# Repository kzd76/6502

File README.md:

# 6502
Yet another Ben Eater sbc clone

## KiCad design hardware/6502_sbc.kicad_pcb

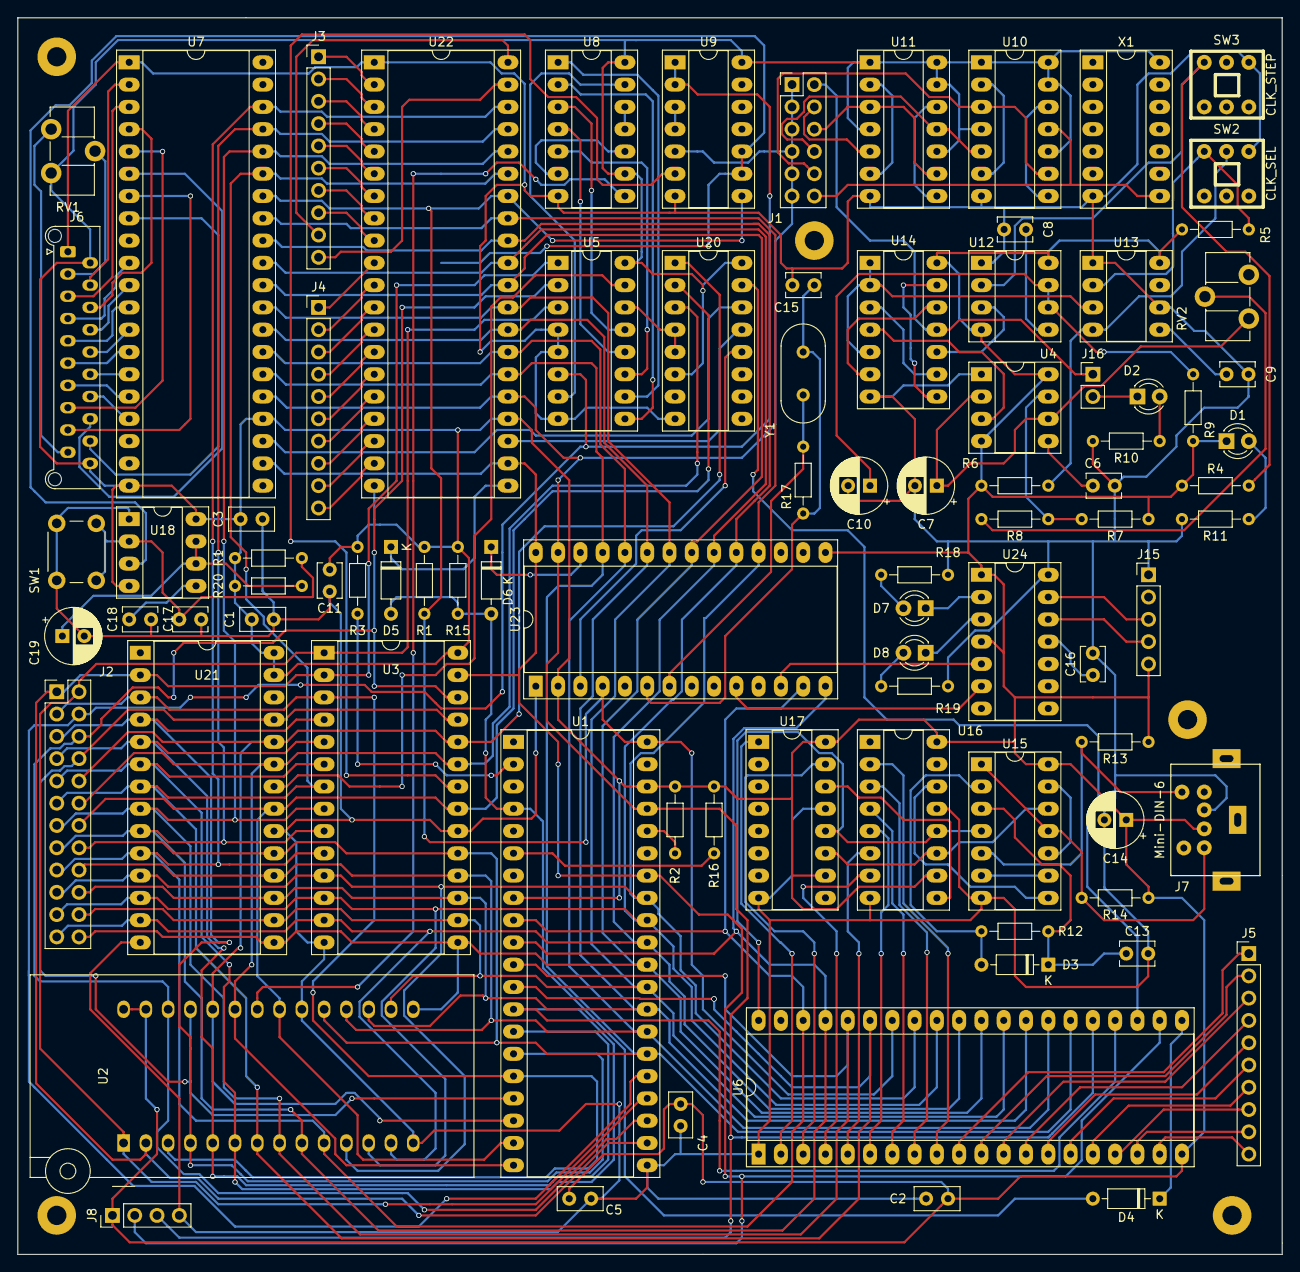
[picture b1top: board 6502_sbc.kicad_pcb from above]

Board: 2 copper layers, 144.1 x 141.0 mm, 92 parts (0 on the bottom side), 162 nets.

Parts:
C1, C2, C3, C4, C5: 100nF; C_Disc_D5.0mm_W2.5mm_P2.50mm
C6, C8, C9, C11, C13, C18: 0.01uF; C_Disc_D3.8mm_W2.6mm_P2.50mm
C7, C10: 1uF; CP_Radial_D6.3mm_P2.50mm
C14, C19: 10uF; CP_Radial_D6.3mm_P2.50mm
C15: 20pF; C_Disc_D3.8mm_W2.6mm_P2.50mm
C16: 470nF; C_Disc_D3.8mm_W2.6mm_P2.50mm
C17: 0.1uF; C_Disc_D3.8mm_W2.6mm_P2.50mm
D1, D2: LED; LED_D3.0mm
D3: 1N4148; D_DO-35_SOD27_P7.62mm_Horizontal
D4, D5, D6: SB140; D_DO-35_SOD27_P7.62mm_Horizontal
D7: LED_Rx; LED_D3.0mm
D8: LED_Tx; LED_D3.0mm
H1, H2, H3, H4, H5: MountingHole; MountingHole_2.2mm_M2_Pad
J1: CLK select; PinHeader_2x06_P2.54mm_Vertical
J2: Debug; PinHeader_2x12_P2.54mm_Vertical
J3: V3PA; PinHeader_1x10_P2.54mm_Vertical
J4: V3PB; PinHeader_1x10_P2.54mm_Vertical
J5: PORTA; PinHeader_1x10_P2.54mm_Vertical
J6: LCD; Molex_Picoflex_90325-0020_2x10_P1.27mm_Vertical
J7: Mini-DIN-6; Mini_din6
J8: SUP; PinHeader_1x04_P2.54mm_Vertical
J15: USB; PinHeader_1x05_P2.54mm_Vertical
J16: LED_EN; PinHeader_1x02_P2.54mm_Vertical
R1, R9, R17: 1M; R_Axial_DIN0204_L3.6mm_D1.6mm_P7.62mm_Horizontal
R1#2, R2, R3, R15, R16: 3.3k; R_Axial_DIN0204_L3.6mm_D1.6mm_P7.62mm_Horizontal
R4, R5, R6, R7, R8: 1k; R_Axial_DIN0204_L3.6mm_D1.6mm_P7.62mm_Horizontal
R10, R11, R18, R19: 220; R_Axial_DIN0204_L3.6mm_D1.6mm_P7.62mm_Horizontal
R12: 33k; R_Axial_DIN0204_L3.6mm_D1.6mm_P7.62mm_Horizontal
R13, R14: 5.6k; R_Axial_DIN0204_L3.6mm_D1.6mm_P7.62mm_Horizontal
R20: 47k; R_Axial_DIN0204_L3.6mm_D1.6mm_P7.62mm_Horizontal
RV1: R_POT; Potentiometer_ACP_CA9-H5_Horizontal
RV2: 1M; Potentiometer_ACP_CA9-H5_Horizontal
SW1: RESET; SW_PUSH_6mm_H5mm
SW2: CLK_SEL; BOTAO4
SW3: CLK_STEP; BOTAO4
U1: W65C02SxP; DIP-40_W15.24mm_Socket_LongPads
U2: 28C256; DIP_Socket-28_W11.9_W12.7_W15.24_W17.78_W18.5_3M_228-1277-0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
U3: HM62256BLP-7; DIP-28_W15.24mm_Socket_LongPads
U4, U12, U13, U18: NE555; DIP-8_W7.62mm_Socket_LongPads
U5, U20: 74LS138; DIP-16_W7.62mm_Socket_LongPads
U6, U7: W65C22SxP; DIP-40_W15.24mm_Socket_LongPads
U8: 74LS11; DIP-14_W7.62mm_Socket_LongPads
U9, U14: 74LS00; DIP-14_W7.62mm_Socket_LongPads
U10, U11: 74HC74; DIP-14_W7.62mm_Socket_LongPads
U15: 74HC14; DIP-14_W7.62mm_Socket_LongPads
U16, U17: 74HC595; DIP-16_W7.62mm_Socket_LongPads
U21: 28C64; DIP-28_W15.24mm_Socket_LongPads
U22: W65C22SxP-65xx; DIP-40_W15.24mm_Socket_LongPads
U23: W65C51-65xx; DIP-28_W15.24mm_Socket_LongPads
U24: MCP2221; DIP-14_W7.62mm_Socket_LongPads
X1: CXO_DIP14; DIP-14_W7.62mm_Socket_LongPads
Y1: 1,8432MHz; Crystal_HC18-U_Vertical

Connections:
+5V: C1.1, C2.1, C3.1, C4.1, C5.1, C11.2, C14.1, D1.1, J6.2, J6.20, J7.4, J8.1, J15.5, R1.1, R1#2.1, R2.1, R3.2, R4.1, R5.1, R6.1, R7.1, R9.1, R13.1, R14.1, R15.2, R16.2, R20.1, RV1.3, U1.8, U1.38, U2.27, U2.28, U3.28, U4.4, U4.8, U5.16, U6.20, U7.20, U7.24, U8.9, U8.14, U9.14, U10.1, U10.4, U10.10, U10.13, U10.14, U11.1, U11.4, U11.10, U11.13, U11.14, U12.4, U12.8, U13.8, U14.14, U15.14, U16.10, U16.16, U17.10, U17.16, U18.4, U18.8, U20.6, U20.16, U21.27, U21.28, U22.20, U22.24, U23.2, U23.15, U24.1, U24.4, X1.14
/0x9000: U5.14, U20.4, U20.5
/0x9000_LCD_VIA: U7.23, U20.14
/0x9200_KBD_VIA: U6.23, U20.15
/0x9400_3rd_VIA: U20.13, U22.23
/0x9600_ACIA: U20.12, U23.3
/0xA000: U5.13, U8.3
/0xB000: U5.12, U8.4
/0xC000: U5.11, U8.5
/0xD000: U5.10, U8.1
/0xE000: U5.9, U8.2
/0xF000: U5.7, U8.13
/A0: J2.17, U1.9, U2.10, U3.10, U6.38, U7.38, U21.10, U22.38, U23.13
/A1: J2.15, U1.10, U2.9, U3.9, U6.37, U7.37, U21.9, U22.37, U23.14
/A2: J2.13, U1.11, U2.8, U3.8, U6.36, U7.36, U21.8, U22.36
/A3: J2.11, U1.12, U2.7, U3.7, U6.35, U7.35, U21.7, U22.35
/A4: J2.9, U1.13, U2.6, U3.6, U6.24, U21.6
/A5: J2.7, U1.14, U2.5, U3.5, U21.5
/A6: J2.5, U1.15, U2.4, U3.4, U21.4
/A7: J2.3, U1.16, U2.3, U3.3, U21.3
/A8: J2.8, U1.17, U2.25, U3.25, U21.25
/A9: J2.10, U1.18, U2.24, U3.24, U20.1, U21.24
/A10: J2.14, U1.19, U2.21, U3.21, U20.2, U21.21
/A11: J2.12, U1.20, U2.23, U3.23, U20.3, U21.23
/A12: J2.1, U1.22, U2.2, U3.2, U5.1, U21.2
/A13: J2.6, U1.23, U2.26, U3.26, U5.2
/A14: J2.2, U1.24, U2.1, U3.1, U5.3
/A15: J2.4, U1.25, U5.6, U9.1, U9.2
/CLK: J1.1, J1.3, J1.5, J1.7, J1.9, J1.11, J8.3, U1.37, U6.25, U7.25, U9.5, U22.25, U23.27
/CLKSEL_1: R5.2, SW2.1, U13.2
/CLKSEL_2: R6.2, SW2.2, U13.4
/CLK_P1: C7.1, RV2.1, U4.2, U4.6
/CLK_P2: R8.2, RV2.2
/D0: J2.19, U1.33, U2.11, U3.11, U6.33, U7.33, U21.11, U22.33, U23.18
/D1: J2.21, U1.32, U2.12, U3.12, U6.32, U7.32, U21.12, U22.32, U23.19
/D2: J2.23, U1.31, U2.13, U3.13, U6.31, U7.31, U21.13, U22.31, U23.20
/D3: J2.24, U1.30, U2.15, U3.15, U6.30, U7.30, U21.15, U22.30, U23.21
/D4: J2.22, U1.29, U2.16, U3.16, U6.29, U7.29, U21.16, U22.29, U23.22
/D5: J2.20, U1.28, U2.17, U3.17, U6.28, U7.28, U21.17, U22.28, U23.23
/D6: J2.18, U1.27, U2.18, U3.18, U6.27, U7.27, U21.18, U22.27, U23.24
/D7: J2.16, U1.26, U2.19, U3.19, U6.26, U7.26, U21.19, U22.26, U23.25
/IRQ: D4.2, D5.2, D6.2, R15.1, U1.4
/IRQ_ACIA: D6.1, U23.26
/IRQ_VIA3: D5.1, U22.21
/LCDCS0: J6.15, U7.5
/LCDCS1: J6.17, U7.7
/LCDCS2: J6.18, U7.8
/LCDD0: J6.7, U7.10
/LCDD1: J6.8, U7.11
/LCDD2: J6.9, U7.12
/LCDD3: J6.10, U7.13
/LCDD4: J6.11, U7.14
/LCDD5: J6.12, U7.15
/LCDD6: J6.13, U7.16
/LCDD7: J6.14, U7.17
/LCDE: J6.6, U7.4
/LCDRESET: J6.16, U7.6
/LCDRS: J6.4, U7.2
/LCDRW: J6.5, U7.3
/NMI: R16.1, U1.6
/RAM: U3.22, U9.6
/RESET: R1#2.2, U1.40, U6.34, U7.34, U9.8, U22.34, U23.4
/ROM: U2.22, U8.8
/RW: J8.2, U1.34, U3.27, U6.22, U7.22, U22.22, U23.28
/VEE: J6.19, RV1.1
/VIA1IRQ: D4.1, U6.21
GND: C1.2, C2.2, C3.2, C4.2, C5.2, C6.2, C7.2, C8.2, C9.2, C10.2, C11.1, C13.2, C14.2, C15.2, C16.2, C17.2, C18.2, C19.2, J6.1, J7.3, J8.4, J15.1, R10.2, R11.2, R18.1, R19.1, SW1.1, SW2.3, SW3.3, U1.21, U2.14, U2.20, U3.14, U3.20, U4.1, U5.4, U5.5, U5.8, U6.1, U7.1, U8.7, U9.7, U10.7, U11.7, U12.1, U13.1, U13.6, U14.7, U15.7, U16.8, U16.13, U17.8, U17.13, U18.1, U20.8, U21.14, U21.20, U22.1, U23.1, U24.14, X1.7
KBD_D0: U6.2, U17.1
KBD_D1: U6.3, U17.15
KBD_D2: U6.4, U16.7
KBD_D3: U6.5, U16.6
KBD_D4: U6.6, U16.5
KBD_D5: U6.7, U16.4
KBD_D6: U6.8, U16.3
KBD_D7: U6.9, U16.2
KBD_IRQ: U6.40, U15.4, U16.12, U17.12
unnamed: C6.1, U4.5
unnamed: C8.1, U12.5
unnamed: C9.1, U13.5
unnamed: C10.1, R9.2, U12.6, U12.7
unnamed: C13.1, D3.1, R12.1, U15.3
unnamed: C15.1, R17.2, U23.6, Y1.1
unnamed: C16.1, U24.11
unnamed: C17.1, R1.2, SW1.2, U18.2
unnamed: C18.1, U18.5
unnamed: C19.1, R20.2, U18.6, U18.7
unnamed: D1.2, R11.1
unnamed: D2.1, J16.2
unnamed: D2.2, R10.1
unnamed: D3.2, R12.2, U15.2
unnamed: D7.1, U24.2
unnamed: D7.2, R18.2
unnamed: D8.1, U24.3
unnamed: D8.2, R19.2
unnamed: J1.2, J16.1, U14.11
unnamed: J1.4, U11.5
unnamed: J1.6, U11.3, U11.9
unnamed: J1.8, U10.5, U11.11
unnamed: J1.10, U10.3, U10.9
unnamed: J1.12, U10.11, X1.8
unnamed: J3.1, U22.2
unnamed: J3.2, U22.3
unnamed: J3.3, U22.4
unnamed: J3.4, U22.5
unnamed: J3.5, U22.6
unnamed: J3.6, U22.7
unnamed: J3.7, U22.8
unnamed: J3.8, U22.9
unnamed: J3.9, U22.40
unnamed: J3.10, U22.39
unnamed: J4.1, U22.10
unnamed: J4.2, U22.11
unnamed: J4.3, U22.12
unnamed: J4.4, U22.13
unnamed: J4.5, U22.14
unnamed: J4.6, U22.15
unnamed: J4.7, U22.16
unnamed: J4.8, U22.17
unnamed: J4.9, U22.18
unnamed: J4.10, U22.19
unnamed: J5.1, U6.10
unnamed: J5.2, U6.11
unnamed: J5.3, U6.12
unnamed: J5.4, U6.13
unnamed: J5.5, U6.14
unnamed: J5.6, U6.15
unnamed: J5.7, U6.16
unnamed: J5.8, U6.17
unnamed: J5.9, U6.18
unnamed: J5.10, U6.19
unnamed: J6.3, RV1.2
unnamed: J7.1, R13.2, U15.5
unnamed: J7.5, R14.2, U15.1, U15.11
unnamed: R2.2, U1.36
unnamed: R3.1, U1.2
unnamed: R4.2, SW3.1, U12.2
unnamed: R7.2, R8.1, U4.7
unnamed: R17.1, U23.7, Y1.2
unnamed: U8.6, U8.10
unnamed: U8.11, U8.12
unnamed: U9.3, U9.4
unnamed: U10.2, U10.6
unnamed: U10.8, U10.12
unnamed: U11.2, U11.6
unnamed: U11.8, U11.12
unnamed: U14.3, U14.9
unnamed: U14.6, U14.12
unnamed: U14.8, U14.13
unnamed: U15.6, U15.9
unnamed: U15.8, U16.14
unnamed: U15.10, U15.13
unnamed: U15.12, U16.11, U17.11
unnamed: U16.9, U17.14
unnamed: U9.9, U9.10, U18.3
unnamed: U23.10, U24.6
unnamed: U23.12, U24.5
Q_1: U4.3, U14.4
Q_2: U12.3, U14.10
Q_3: U13.3, U14.1, U14.2, U14.5
ROM2: U5.15, U21.22
USB_D+: J15.3, U24.13
USB_D-: J15.4, U24.12

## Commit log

2025-04-08 Rename README.MD to README.md
2025-04-09 Add files via upload
    LCD scroll works, BASIC starts, PRINT, LIST, NEW, RUN works
2025-04-12 Rename barna_bios.s to bios.s
2025-04-12 Rename barna_char_rom.s to char_rom.s
2025-04-14 Add files via upload
    emu
